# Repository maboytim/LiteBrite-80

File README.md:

# LiteBrite-80

The LiteBrite-80 (LB-80) is a memory visualization gadget for Z80 systems.  It displays the 1k (8x8 display) or 256 (16x16 display) byte block being accessed by the Z80 (code and data read/write).  It is primarily intended for Z80 based TRS-80 systems (Models 1, 2 (12, etc), 3, and 4) but is applicable to any Z80 based system.

The LB-80 consists of two parts - a Z80 adapter and a display.  The Z80 adapter is a small PCB in which the Z80 is installed and replaces the Z80.  Ideally the Z80 is socketed in the host machine and the LB-80 is just installed in the socket - otherwise the Z80 must be removed and the LB-80 installed in its place or replaced with a socket.  The adapter has a connector to attach a display.  The display is a small PCB that contains an 8x8 or 16x16 LED array that can either plug directly into the adapter or more likely connected to the adapter via a cable so that the display can be located for convenient viewing.

## Theory Of Operation

The operation is very simple.  The 8 address msb's (A8-A15) are latched at the beginning of a memory read or write cycle and are used to light a single LED on a row/column display.  For an 8x8 display the addresses A13-A15 are decoded with a 1-of-8 decoder to select the row, and addresses A10-A12 are decoded with a 1-of-8 decoder to select the column - which in turn light the single LED at the selected row and column position.  The lower-left LED corresponds to the lowest address range and the upper-right LED corresponds to the highest address range.

In normal operation the Z80's address will change very rapidly so the LED's will flash very rapidly - which your eyes will average such that the LED's will appear lit with a brightness proportional to the percentage of time the Z80 accesses memory in the corresponding region over the averaging time of your eyes.

The addresses are latched at the *beginning* of the memory cycle as opposed to the end so that if the cycle is extended by WAIT it will be properly reflected by the corresponding LED.

For a 16x16 display A12-A15 would be decoded for the row and A8-A11 for the column.

## Adapter PCB

The adapter PCB design is available [here](kicad/Visual80-3).  The design is intended to be as compact as possible so to fit into about the space of the Z80 itself.  To achieve this the design is essentially a 40-pin socket - but with a small protrusion for the display connector.  The adapter could be used in place of a Z80 socket, or if installed in a socket is equivalent to stacking a second socket on top of the socket.

Adapter PCB installed in TRS-80 M3:

The design uses individual machine socket pins which can be removed from a machine socket or bare pins can be purchased.  The pins should be inserted in the PCB until the collar touches the top of the PCB - they might have a slight interference fit and need to be pressed into the PCB.

The connector pinout is compatible with the PMOD connector common to FPGA development boards.  The PMOD connector is simply a 2x6 connector with two GND pins, two Vcc pins, and eight signal pins.  For an 8x8 display only six signals are needed so a pinout that allows for a 10-pin connector for 8x8 display is used - this allows for use of a 10-pin cable when connecting the display via a cable.

The use of the PMOD connector also allows the display to be used with many FPGA boards for example if emulating a TRS-80 with an FPGA.

## Display PCB

An 8x8 display PCB design is available [here](kicad/lb-80), and is also in the [TRS-IO project](https://github.com/apuder/TRS-IO/tree/master/kicad/pmod/lb-80).

Here is an earlier version of the display - connected to TRS-80 M3 booted to the FreHD menu:

The 8x8 displays can be arranged into larger arrays so a 16x16 display can be made from four 8x8 displays.  I've personally not made a 16x16 display.

## Software

No special software is needed because the LB-80 just displays the natural behavior of the Z80 activity.  The resultant patterns are interesting and fun to watch but also often lend insight into what the Z80 is doing.

However, it is possible to contrive a program that generates certain patterns on the LB-80 display.  To light an individual dot on an 8x8 display requires that the Z80 be limited to the corresponding 1k block of memory (program, data, and stack).  To light a different individual LED would require the Z80 be limited to a different corresponding 1k block of memory.  To not light an LED would require the Z80 not touch the corresponding 1k block of memory.  So contriving such a program is tricky but can be done.

### Marquee Display Program

A TRS-80 program [lb80text](source/lb80text) that displays scrolling marquee style text on the LB-80 is provided as one such example.  See the source code for detailed explanation of how the program works.  Several versions are provided.

The command syntax is `lb80text "string to display"`.  The quotes are optional and only required if the string has leading spaces.

It happens that this demo program is a good stress case for memory.  Although using additional banked memory in the M4 and M2 really has no effect on the operation of the LB-80 itself some banked versions are included.  If the program doesn't crash your Z80 and memory system are likely pretty solid.

#### [TRS-80 Model 1 and Model 3 Version](source/lb80text/lb80txm1.asm)

For TRS-80 M1 with lowercase mod and 48k RAM, and M3 with 48k.  See source code for M1 without lowercase mod.

#### [TRS-80 Model 4 Version](source/lb80text/lb80txm4.asm)

For TRS-80 M4 with 64k.

#### [TRS-80 Model 2 Version](source/lb80text/lb80txm2.asm)

For TRS-80 M2 with 64k.  Very similar to M4 version but doesn't use display memory since the M2 can't run from display memory.

#### TRS-80 Model 4 128k Version

Coming...

#### [TRS-80 Model 2 512k Version](source/lb80text/lb80512k.asm)

For TRS-80 M2 with 512k.  A M2 (M12, etc) with 512k is a rare beast but if you are one of the lucky few with a [512k card by Ruud](https://www.youtube.com/watch?v=_I01NHzUzNk) this will give you something to test it with.  (Note: I also have a 512k card of my own design that's not yet ready for primetime but is my personal motivation for this version).

## Alternative Adapter Implementations

In systems that expose the Z80 bus an LB-80 adapter that connects to the bus rather than directly to the Z80 is possible.  Such systems include:
* TRS-80 Model 1
* TRS-80 Model 2 (12, etc)
* S100

The TRS-80 M2 (M12, etc) is an interesting case because the address bus is inverted.  It might seem that an LB-80 adapter would have to invert the address signals but that's actually not required.  Inverting both the row and column signals results in the display being rotated 180 degrees so all that's needed is to rotate the display 180 degrees to obtain the intended orientation.

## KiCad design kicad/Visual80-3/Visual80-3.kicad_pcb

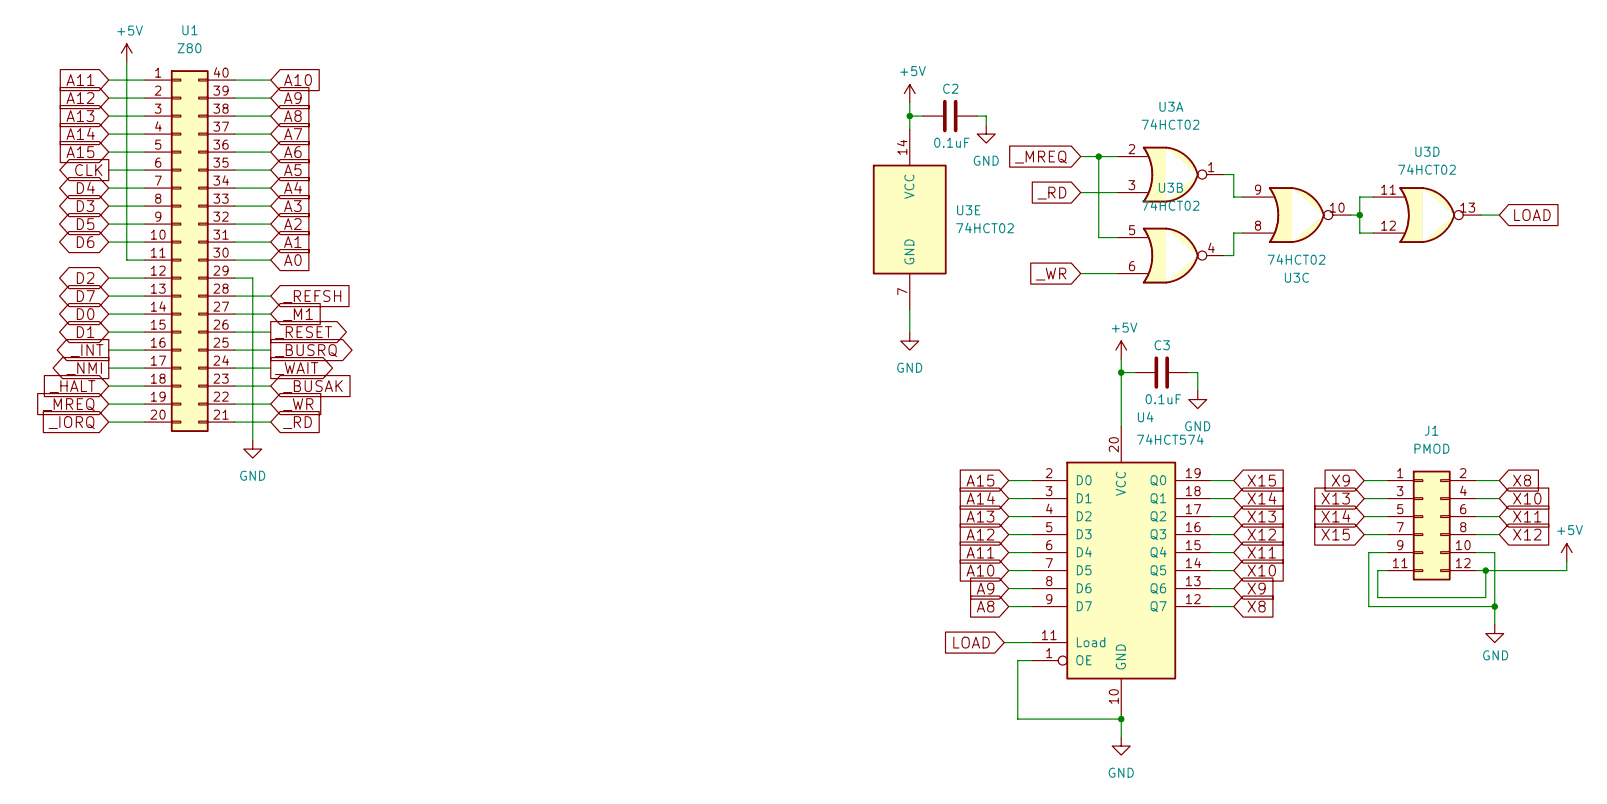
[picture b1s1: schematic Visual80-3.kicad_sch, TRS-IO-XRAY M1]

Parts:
C2, C3: 0.1uF; C_0805_2012Metric_Pad1.18x1.45mm_HandSolder
J1: PMOD; PinSocket_2x06_P2.54mm_Vertical
U1: Z80; DIP-40_W15.24mm
U3: 74HCT02; TSSOP-14_4.4x5mm_P0.65mm
U4: 74HCT574; TSSOP-20_4.4x6.5mm_P0.65mm

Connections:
+5V: C2.2, C3.2, J1.11, J1.12, U1.11, U3.14 (VCC), U4.20 (VCC)
A0: U1.30
A1: U1.31
A2: U1.32
A3: U1.33
A4: U1.34
A5: U1.35
A6: U1.36
A7: U1.37
A8: U1.38, U4.9 (D7)
A9: U1.39, U4.8 (D6)
A10: U1.40, U4.7 (D5)
A11: U1.1, U4.6 (D4)
A12: U1.2, U4.5 (D3)
A13: U1.3, U4.4 (D2)
A14: U1.4, U4.3 (D1)
A15: U1.5, U4.2 (D0)
CLK: U1.6
D0: U1.14
D1: U1.15
D2: U1.12
D3: U1.8
D4: U1.7
D5: U1.9
D6: U1.10
D7: U1.13
GND: C2.1, C3.1, J1.9, J1.10, U1.29, U3.7 (GND), U4.1 (OE), U4.10 (GND)
LOAD: U3.13, U4.11 (Load)
unnamed: U3.1, U3.9
unnamed: U3.4, U3.8
unnamed: U3.10, U3.11, U3.12
X8: J1.2, U4.12 (Q7)
X9: J1.1, U4.13 (Q6)
X10: J1.4, U4.14 (Q5)
X11: J1.6, U4.15 (Q4)
X12: J1.8, U4.16 (Q3)
X13: J1.3, U4.17 (Q2)
X14: J1.5, U4.18 (Q1)
X15: J1.7, U4.19 (Q0)
_BUSAK: U1.23
_BUSRQ: U1.25
_HALT: U1.18
_INT: U1.16
_IORQ: U1.20
_M1: U1.27
_MREQ: U1.19, U3.2, U3.5
_NMI: U1.17
_RD: U1.21, U3.3
_REFSH: U1.28
_RESET: U1.26
_WAIT: U1.24
_WR: U1.22, U3.6

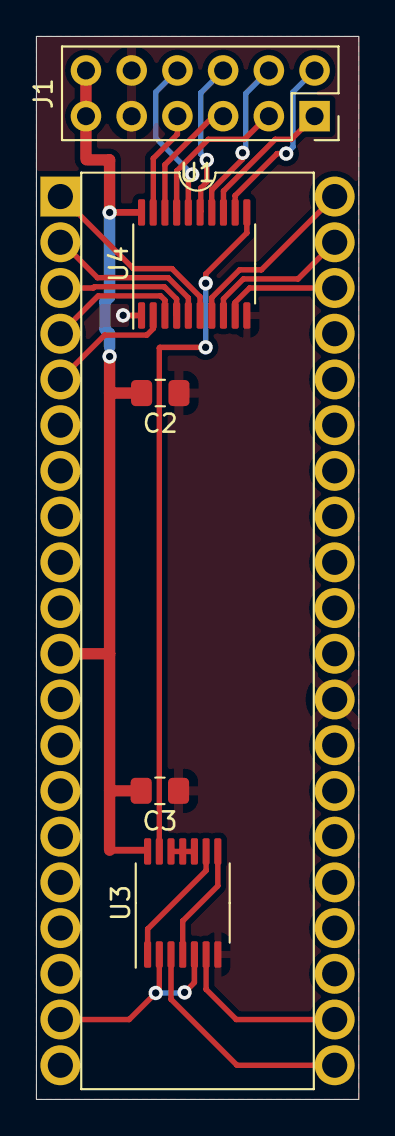
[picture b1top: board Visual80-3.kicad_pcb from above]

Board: 2 copper layers, 17.9 x 59.1 mm, 6 parts (0 on the bottom side), 25 nets.

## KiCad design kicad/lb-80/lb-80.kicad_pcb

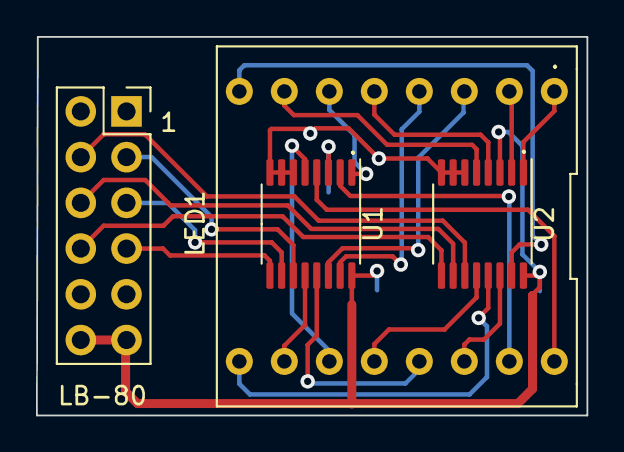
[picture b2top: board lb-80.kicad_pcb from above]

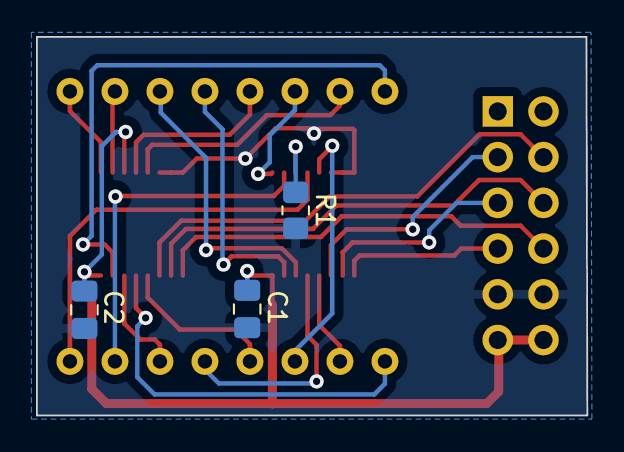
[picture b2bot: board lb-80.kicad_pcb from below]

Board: 2 copper layers, 30.6 x 21.0 mm, 7 parts (3 on the bottom side), 25 nets.

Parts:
C1, C2: 0.1uF; C_0805_2012Metric_Pad1.18x1.45mm_HandSolder
J1: Conn_02x06_Odd_Even; PinSocket_2x06_P2.54mm_Vertical
LED1: 788BS
R1: 150; R_0805_2012Metric_Pad1.20x1.40mm_HandSolder
U1, U2: 74HC4051; TSSOP-16_4.4x5mm_P0.65mm

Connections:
+3V3: C1.1, C2.1, J1.11, J1.12, U1.16 (VCC), U2.3 (A), U2.16 (VCC)
C1: LED1.13 (C1), U1.13 (A0)
C2: LED1.3 (C2), U1.14 (A1)
C3: LED1.4 (C3), U1.15 (A2)
C4: LED1.10 (C4), U1.12 (A3)
C5: LED1.6 (C5), U1.1 (A4)
C6: LED1.11 (C6), U1.5 (A5)
C7: LED1.15 (C7), U1.2 (A6)
C8: LED1.16 (C8), U1.4 (A7)
GND: C1.2, C2.2, J1.9, J1.10, R1.2, U1.6 (~E), U1.7 (VEE), U1.8 (GND), U2.6 (~E), U2.7 (VEE), U2.8 (GND)
unnamed: R1.1, U1.3 (A)
PMOD_IO2_A10: J1.3, U1.11 (S0)
PMOD_IO3_A11: J1.5, U1.10 (S1)
PMOD_IO4_A12: J1.7, U1.9 (S2)
PMOD_IO6_A13: J1.4, U2.11 (S0)
PMOD_IO7_A14: J1.6, U2.10 (S1)
PMOD_IO8_A15: J1.8, U2.9 (S2)
R1: LED1.9 (R1), U2.13 (A0)
R2: LED1.14 (R2), U2.14 (A1)
R3: LED1.8 (R3), U2.15 (A2)
R4: LED1.12 (R4), U2.12 (A3)
R5: LED1.1 (R5), U2.1 (A4)
R6: LED1.7 (R6), U2.5 (A5)
R7: LED1.2 (R7), U2.2 (A6)
R8: LED1.5 (R8), U2.4 (A7)

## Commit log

2025-07-20 Added kicad design. Added demo programs. Updated readme.
2025-07-20 Added M3 512k demo program.
2025-07-21 Added dislay PCB design. Added pictures. Updated readme.
2025-07-21 Added theory of operation.
